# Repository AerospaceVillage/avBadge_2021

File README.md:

# Aerospace Village Badge 2021

This repository is to document and capture all of the engineering and design work that went into creating the [Aerospace Village](https://aerospacevillage.org) Badge for DefCon 2021.

We hope you enjoy all of the ways to interact with this years badge and learn about Aerospace along the way!

## Kit Assembly

Instructions for assembling a kit can be found in the Document folder.

  - [Tindie Instructions](https://github.com/daneallen/avBadge_2021/blob/master/Documents/av_badge2021_instructions.pdf)
  - [Instructions sent with kit](https://github.com/daneallen/avBadge_2021/blob/master/Documents/av_badge2021_kit_instructions.pdf)

  ## Arduino Programming
  Using the Arduino IDE Add the correct Boards Manager URL:

      - Under File->Preferences add the following URL https://mcudude.github.io/MiniCore/package_MCUdude_MiniCore_index.json
      - Then with the new Boards Manager options select MiniCore
          - Select the Atmega88

  Steps:

      - Programmer - USBTinyISP
      - Clock - Internal 8MHZ
      - Bootloader - "No bootloader" (Not enough memory to support the bootloader)
      - Sketch -> Upload

      ## AVR Programming

[device permissions help](https://andreasrohner.at/posts/Electronics/How-to-fix-device-permissions-for-the-USBasp-programmer/)

[ttyACM permission](https://stackoverflow.com/questions/40951728/avrdude-ser-open-cant-open-device-dev-ttyacm0-device-or-resource-busy)

```
sudo adduser <username> dialout
$ sudo chmod a+rw /dev/ttyACM0
```

## Hardware
The ATMega88 is programmed with the [Sparkfun Tiny AVR Programmer](https://www.sparkfun.com/products/11801) using the [SparkFun ISP Pogo Adapter](https://www.sparkfun.com/products/11591)

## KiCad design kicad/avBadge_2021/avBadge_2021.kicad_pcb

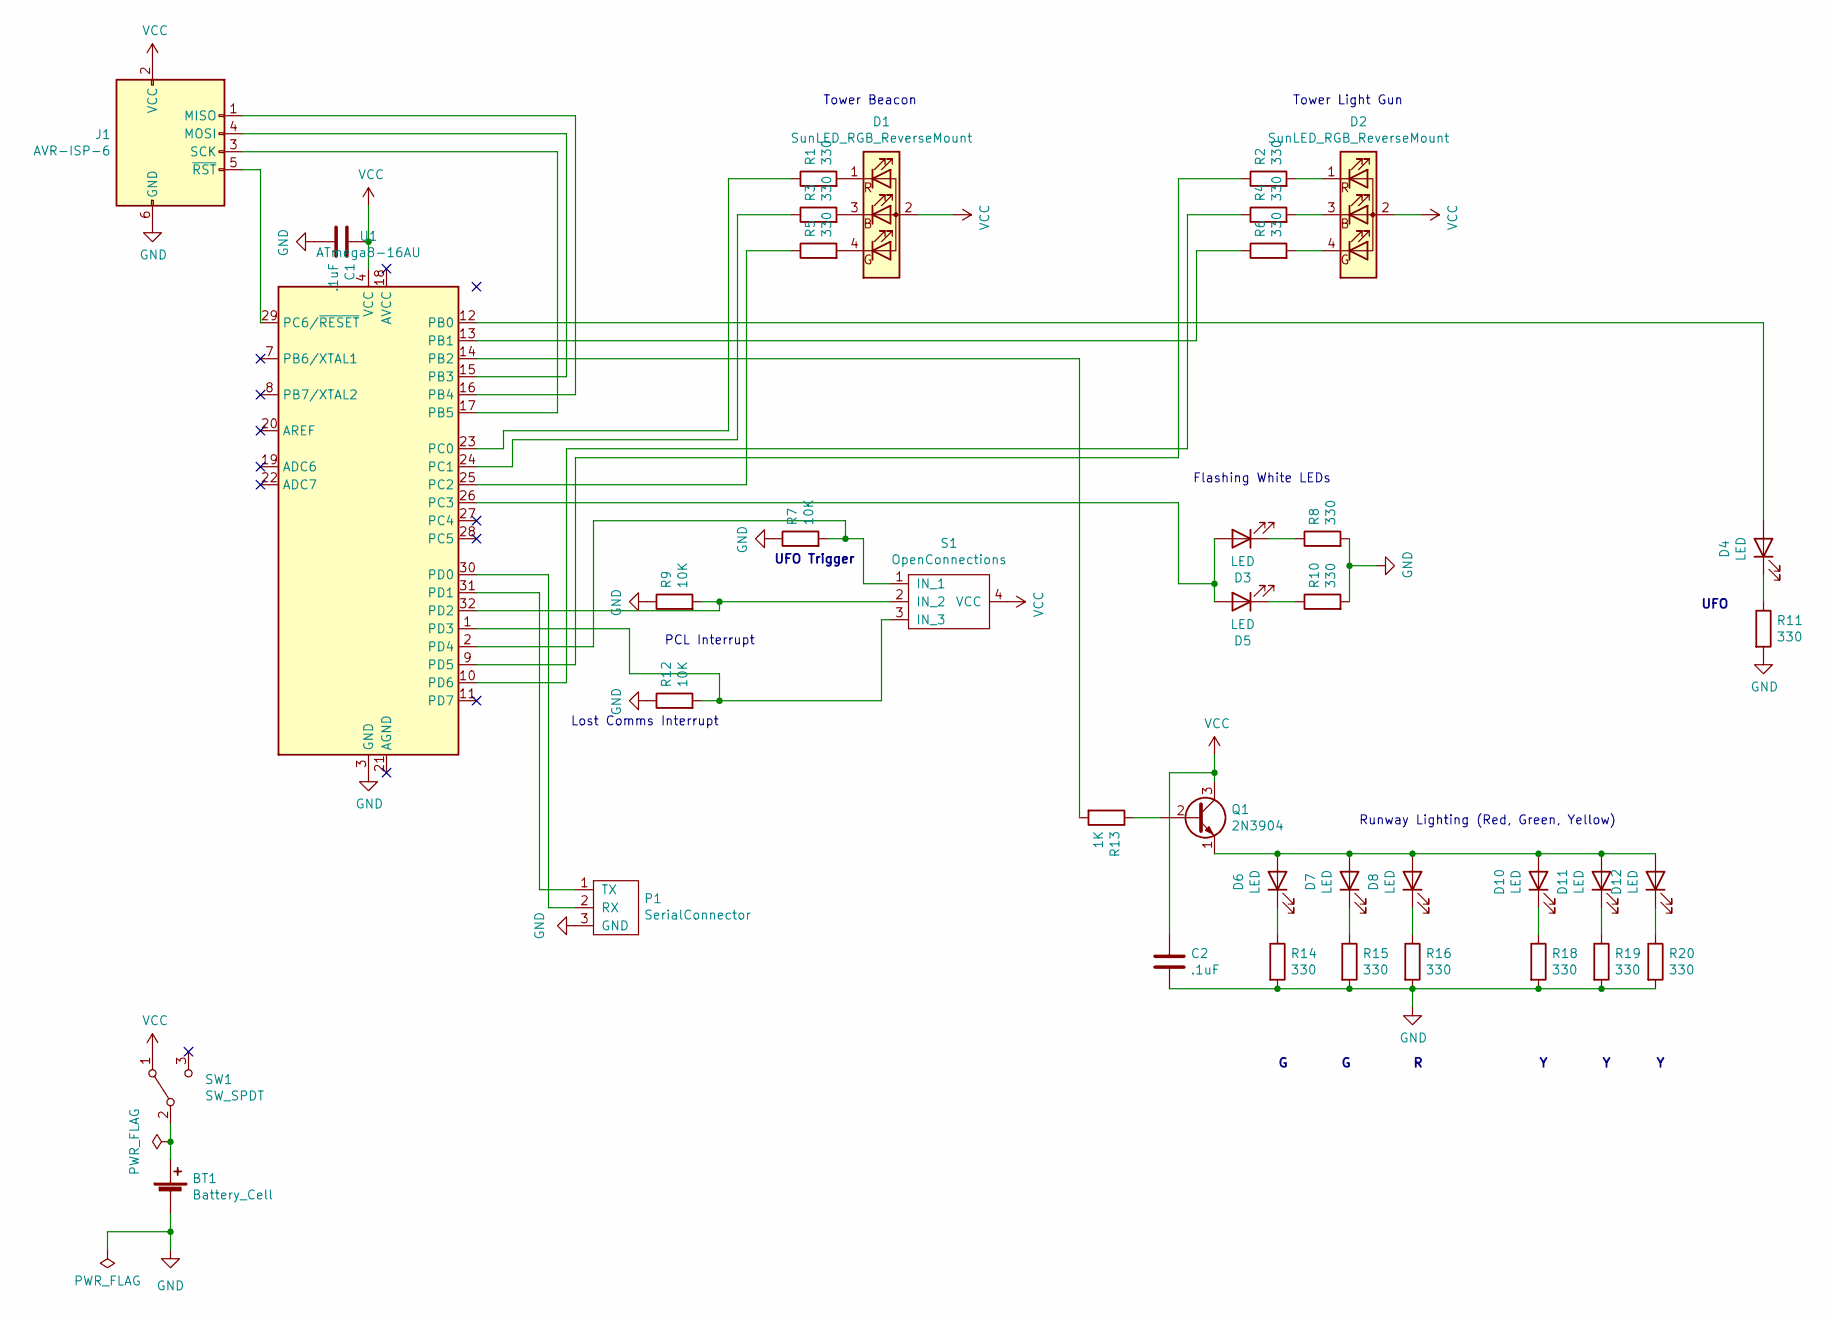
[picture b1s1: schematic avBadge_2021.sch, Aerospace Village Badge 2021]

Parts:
BT1: Battery_Cell; 2479
C1, C2: .1uF; R_1206_3216Metric
D1, D2: SunLED_RGB_ReverseMount; XZMDKCBDDG45S-9
D3, D5: LED; led_in-s124ar
D4: LED; XZFBB45S-9
D6, D7: LED; XZM2CRK45WT-9
D8: LED; XZDGK45WT-9
D10, D11, D12: LED; XZMYK45WT-9
J1: AVR-ISP-6
P1: SerialConnector; serialConnector
Q1: 2N3904; SOT-23-NPN
R1, R2, R3, R4, R5, R6, R8, R10, R11, R14, R15, R16, R18, R19, R20: 330; R_1206_3216Metric
R7, R9, R12: 10K; R_1206_3216Metric
R13: 1K; R_1206_3216Metric
S1: OpenConnections; artboard2
SW1: SW_SPDT; switch_JS202011SCQN
U1: ATmega8-16AU; TQFP-32_7x7mm

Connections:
GND: BT1.2 (-), C1.2, C2.2, J1.6 (GND), P1.3 (GND), R7.1, R8.2, R9.1, R10.2, R11.2, R12.1, R14.2, R15.2, R16.2, R18.2, R19.2, R20.2, U1.3 (GND), U1.5 (GND)
unnamed: BT1.1 (+), SW1.2 (B)
unnamed: D1.1 (R), R1.2
unnamed: D1.3 (G), R3.2
unnamed: D1.4 (B), R5.2
unnamed: D2.1 (R), R2.2
unnamed: D2.3 (G), R4.2
unnamed: D2.4 (B), R6.2
unnamed: D3.1 (K), R8.1
unnamed: D3.2 (A), D5.2 (A), U1.26 (PC3)
unnamed: D4.1 (K), R11.1
unnamed: D4.2 (A), U1.12 (PB0)
unnamed: D5.1 (K), R10.1
unnamed: D6.1 (K), R14.1
unnamed: D7.1 (K), R15.1
unnamed: D8.1 (K), R16.1
unnamed: D10.1 (K), R18.1
unnamed: D6.2 (A), D7.2 (A), D8.2 (A), D10.2 (A), D11.2 (A), D12.2 (A), Q1.1 (E)
unnamed: D11.1 (K), R19.1
unnamed: D12.1 (K), R20.1
unnamed: J1.1 (MISO), U1.16 (PB4)
unnamed: J1.3 (SCK), U1.17 (PB5)
unnamed: J1.4 (MOSI), U1.15 (PB3)
unnamed: J1.5 (~RST), U1.29 (PC6/~RESET)
unnamed: P1.1 (TX), U1.31 (PD1)
unnamed: P1.2 (RX), U1.30 (PD0)
unnamed: Q1.2 (B), R13.1
unnamed: R1.1, U1.23 (PC0)
unnamed: R2.1, U1.9 (PD5)
unnamed: R3.1, U1.24 (PC1)
unnamed: R4.1, U1.10 (PD6)
unnamed: R5.1, U1.25 (PC2)
unnamed: R6.1, U1.13 (PB1)
unnamed: R7.2, S1.1 (IN_1), U1.2 (PD4)
unnamed: R9.2, S1.2 (IN_2), U1.32 (PD2)
unnamed: R12.2, S1.3 (IN_3), U1.1 (PD3)
unnamed: R13.2, U1.14 (PB2)
VCC: C1.1, C2.1, D1.2 (A), D2.2 (A), J1.2 (VCC), Q1.3 (C), S1.4 (VCC), SW1.1 (A), U1.4 (VCC), U1.6 (VCC)

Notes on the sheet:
Tower Beacon
Tower Light Gun
Flashing White LEDs
Runway Lighting (Red, Green, Yellow)
PCL Interrupt
Lost Comms Interrupt
UFO
UFO Trigger

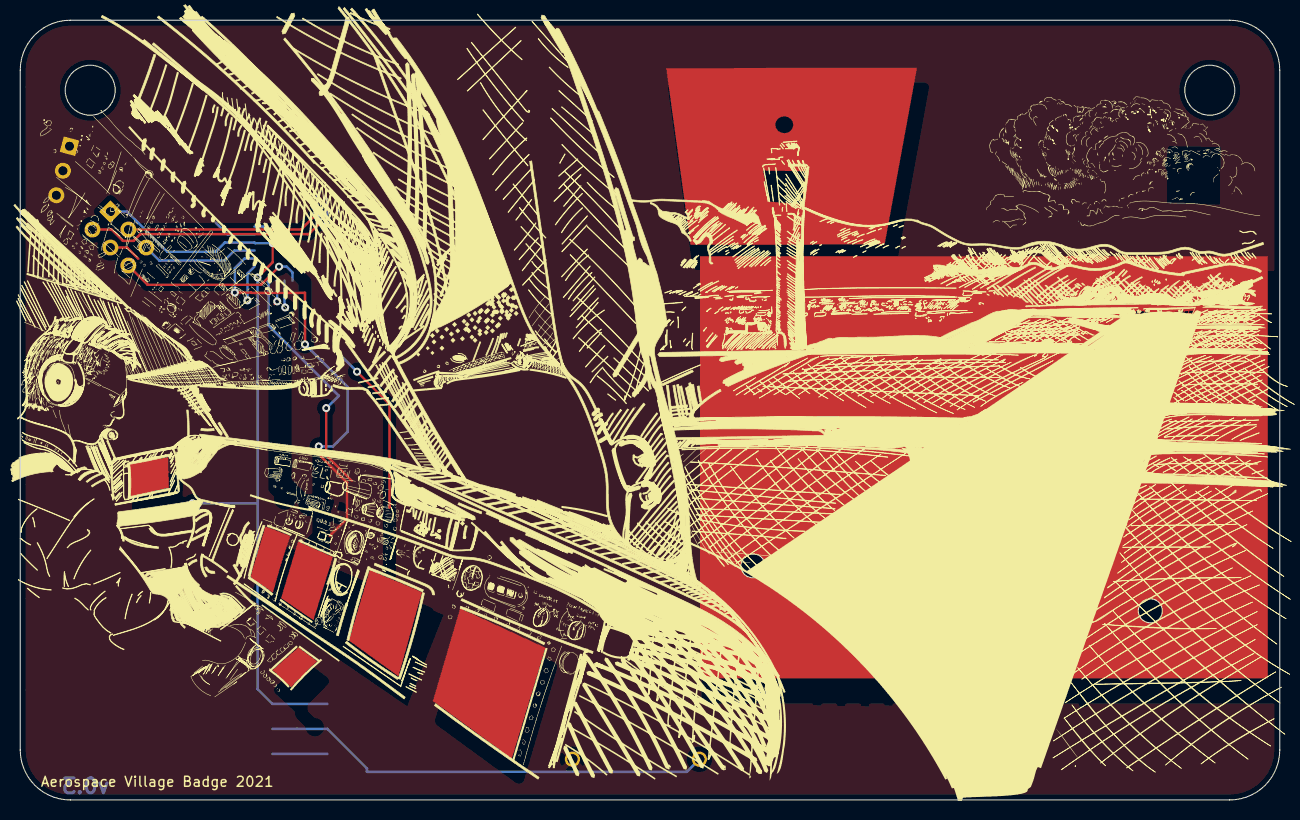
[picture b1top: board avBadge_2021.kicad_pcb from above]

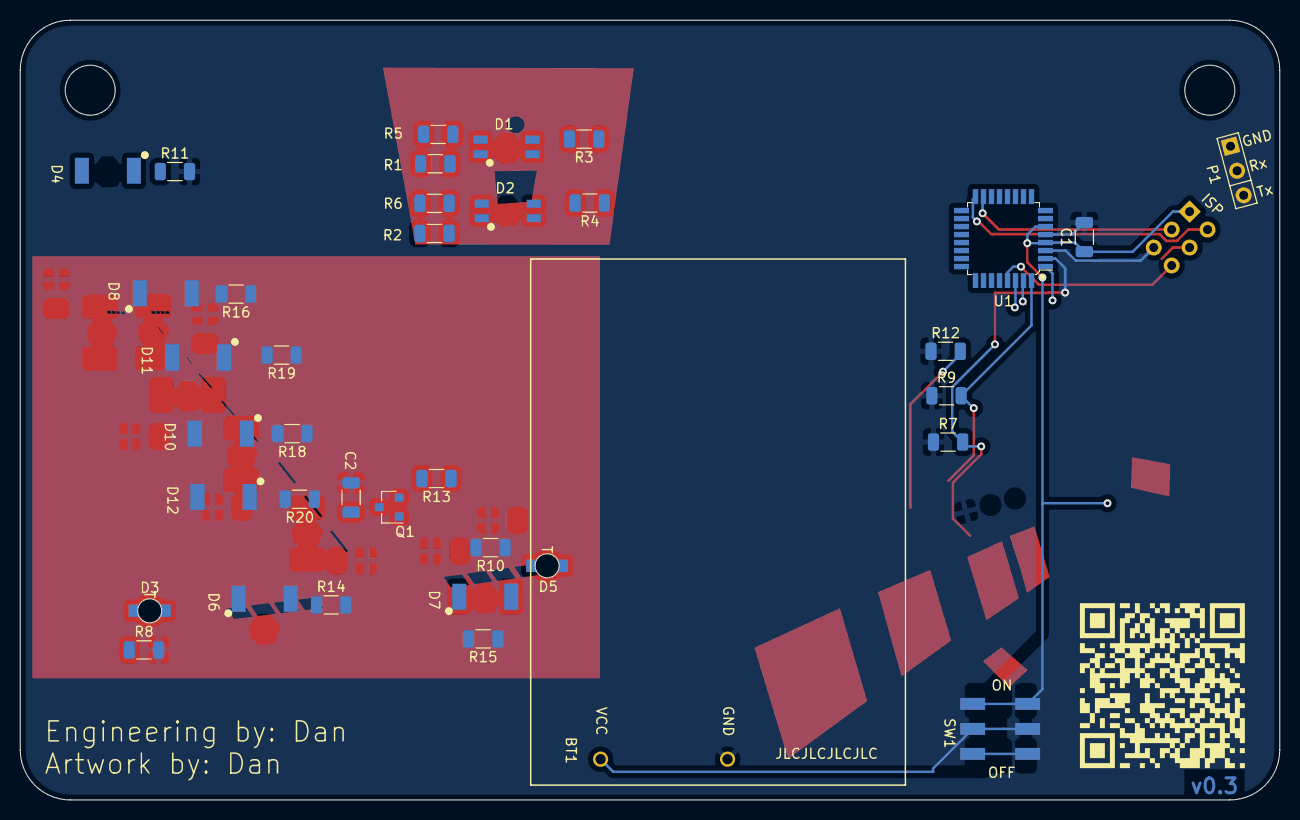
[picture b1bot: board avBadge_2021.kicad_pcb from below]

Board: 2 copper layers, 126.0 x 78.0 mm, 40 parts (38 on the bottom side), 38 nets.

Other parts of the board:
QR*****: qrc

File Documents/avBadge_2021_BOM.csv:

Reference, Quantity, Value, Footprint
BT1 ,1,Battery_Cell,2479_battery_holder:2479
C1 C2 ,2,.1uF,Resistors_SMD:R_1206_3216Metric
D1 D2 ,2,SunLED_RGB_ReverseMount,sunled:XZMDKCBDDG45S-9
D10 D11 D12 ,3,Yellow LED,sunled:XZMYK45WT-9
D4 D9 ,2,Blue LED,sunled:XZFBB45S-9
D3 D5 ,2,White LED,aerospace_badge:led_in-s124ar
D6 D7 ,2,Green LED,sunled:XZM2CRK45WT-9
D8 ,1,Red LED,sunled:XZDGK45WT-9
J1 ,1,AVR-ISP-6,aerospace_badge:AVR-ISP-6
P1 ,1,SerialConnector,aerospace_badge:serialConnector
Q1 ,1,2N3904,aerospace_badge:SOT-23-NPN
R13 ,1,1K,Resistors_SMD:R_1206_3216Metric
R1 R2 R3 R4 R5 R6 R8 R10 R11 R14 R15 R16 R17 R18 R19 R20 ,16,330,Resistors_SMD:R_1206_3216Metric
R7 R9 R12 ,3,10K,Resistors_SMD:R_1206_3216Metric
S1 ,1,OpenConnections,aerospace_badge:artboard_smooth2
SW1 ,1,SW_SPDT,aerospace_badge:switch_JS202011SCQN
U1 ,1,ATmega8-16AU,digikey-footprints:TQFP-32_7x7mm

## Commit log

2021-04-21 initial commit for prototype badge
2021-05-01 arduino code updates and manufactured v01 gerbers completed.
2021-05-05 arduino update to include pulsing lights as desired.
2021-05-07 refactor of kicad files working through incorporation of art and new MCU design.
2021-05-07 v0.2 gerber builtout and sent for fabrication.
2021-05-12 config changes.
2021-05-12 config settings.
2021-05-12 attempt 1 at simplifying artwork
2021-05-25 incremental improvements to art, edgecuts, layout
2021-05-26 artwork cleanup and general tweaks. Incremental save.
2021-05-29 v03. Updated art and everything that goes along.
2021-06-09 multiple changes, now on v04
2021-06-09 v04 as sent to for fabrication.
2021-06-17 updated EEPROM usage and F() use
2021-07-07 file organization, Readme update, build instructions.
2021-07-07 rename Images folder and Readme with gif
2021-07-10 script used to program all shipped boards... fingers crossed :-)
2021-07-21 fixed file paths to work
2021-07-22 working attachment for last years badge.
